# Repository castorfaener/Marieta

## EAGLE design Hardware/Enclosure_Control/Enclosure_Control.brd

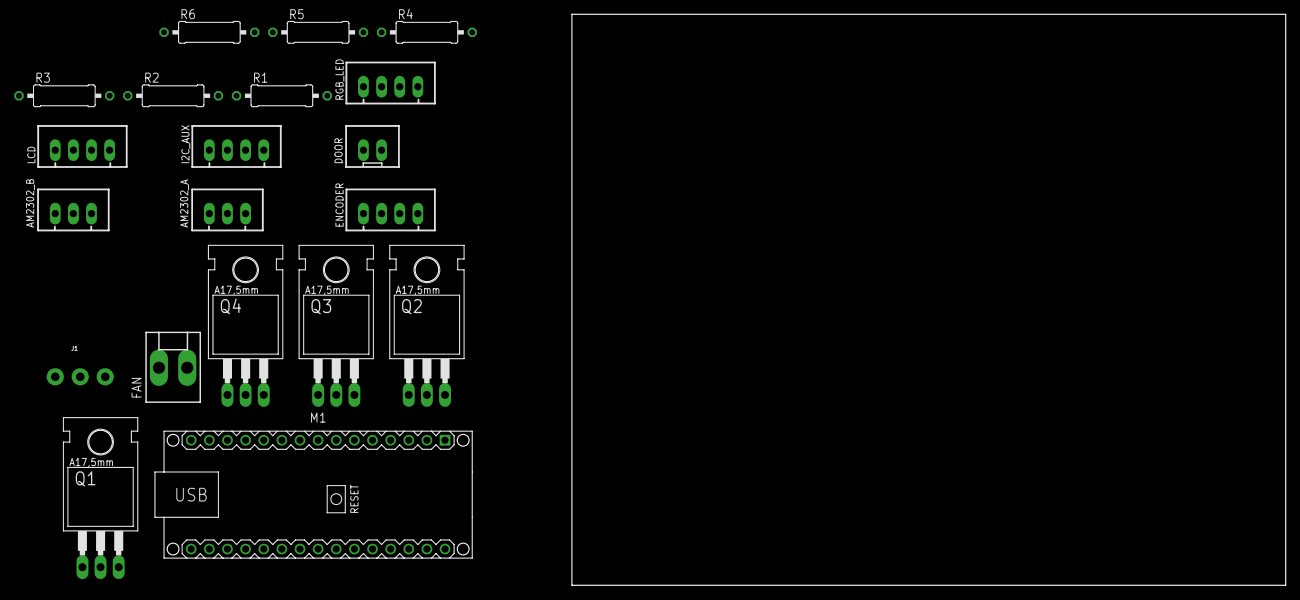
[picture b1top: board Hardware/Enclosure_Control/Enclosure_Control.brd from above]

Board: 2 copper layers, 100.0 x 80.0 mm, 20 parts (0 on the bottom side), 20 nets, no tracks yet.

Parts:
AM2302_A, AM2302_B: JST-XH-03-PIN-LONG-PAD; JST-XH-03-PACKAGE-LONG-PAD
DOOR: JST-XH-02-PIN-LONG-PAD; JST-XH-02-PACKAGE-LONG-PAD
ENCODER: JST-XH-04-PIN-LONG-PAD; JST-XH-04-PACKAGE-LONG-PAD
FAN: KK-156-2
I2C_AUX: JST-XH-04-PIN-LONG-PAD; JST-XH-04-PACKAGE-LONG-PAD
J1: SCREWTERMINAL-3.5MM-3-NS
LCD: JST-XH-04-PIN-LONG-PAD; JST-XH-04-PACKAGE-LONG-PAD
M1: ARDUINO-NANO-3.0
Q1, Q2, Q3, Q4: IRF3704; TO220AH
R1, R6: 0309/12
R2, R3, R4, R5: 10k; 0309/12
RGB_LED: JST-XH-04-PIN-LONG-PAD; JST-XH-04-PACKAGE-LONG-PAD

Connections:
+5V: AM2302_A.1, AM2302_B.1, DOOR.1, I2C_AUX.1, J1.2, LCD.1, M1.J2.1
+12V: FAN.1, J1.3, RGB_LED.1
DHT22_A: AM2302_A.3, M1.J1.11
DHT22_B: AM2302_B.3, M1.J1.10
DOOR_S: DOOR.2, M1.J1.7, R1.2
FAN: M1.J1.13, R5.1
GND: AM2302_A.2, AM2302_B.2, I2C_AUX.2, J1.1, LCD.2, M1.J2.2, Q4.E, R1.1
G_LED: M1.J1.8, R3.1, R4.1
unnamed: Q1.E, Q2.E, Q3.E
unnamed: Q3.C, RGB_LED.4
unnamed: Q2.C, RGB_LED.3
unnamed: Q1.C, RGB_LED.2
unnamed: Q1.B, R2.2
unnamed: Q2.B, R3.2
unnamed: Q3.B, R4.2
unnamed: FAN.2, Q4.C
unnamed: Q4.B, R5.2
R_LED: M1.J1.9, R2.1
SCL: I2C_AUX.4, LCD.4, M1.J2.7
SDA: I2C_AUX.3, LCD.3, M1.J2.8

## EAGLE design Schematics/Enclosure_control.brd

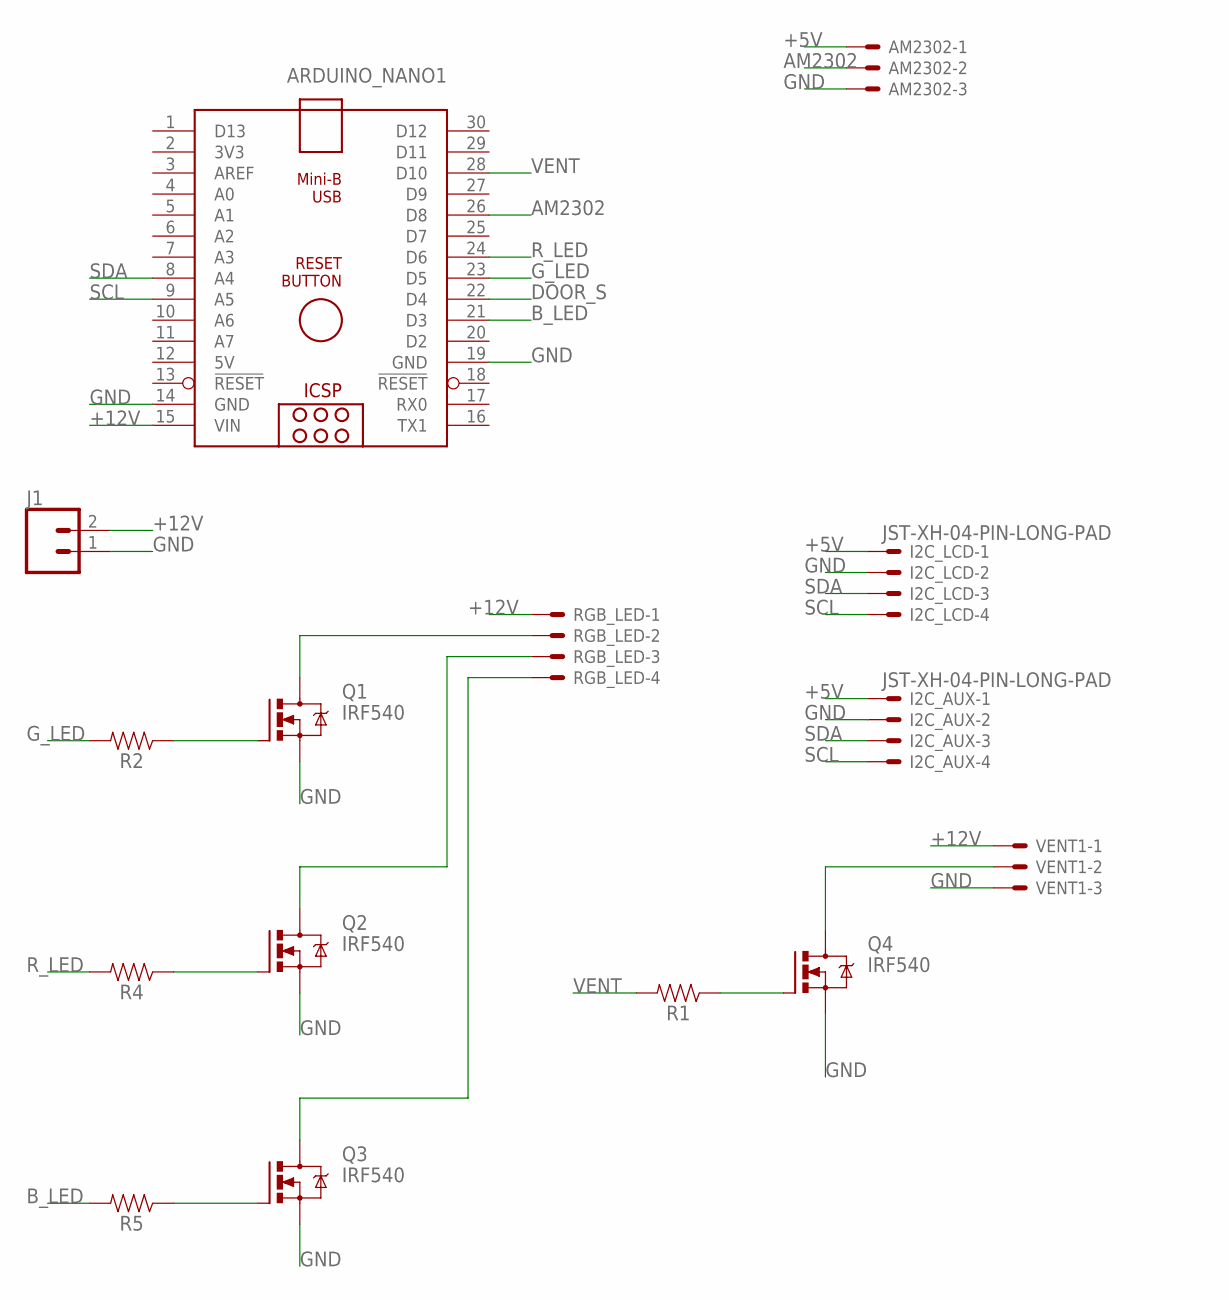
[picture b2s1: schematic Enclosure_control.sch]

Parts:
AM2302: KK-156-3
ARDUINO_NANO1: ARDUINO_NANO
I2C_AUX, I2C_LCD: JST-XH-04-PIN-LONG-PAD; JST-XH-04-PACKAGE-LONG-PAD
J1: CONN_02PTH4; 1X02_XTRA_BIG
Q1, Q2, Q3, Q4: IRF540; TO220BV
R1, R2, R4, R5: AXIAL-0.3
RGB_LED: KK-156-4
VENT1: KK-156-3

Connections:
5V: ARDUINO_NANO1.12 (5V)
+5V: AM2302.1, I2C_AUX.1, I2C_LCD.1
+12V: ARDUINO_NANO1.15 (VIN), J1.2, RGB_LED.1, VENT1.1
AM2302: AM2302.2, ARDUINO_NANO1.26 (D8)
B_LED: ARDUINO_NANO1.21 (D3), R5.P$2 (2)
DOOR_S: ARDUINO_NANO1.22 (D4)
GND: AM2302.3, ARDUINO_NANO1.14 (GND), ARDUINO_NANO1.19 (GND), I2C_AUX.2, I2C_LCD.2, J1.1, Q1.S, Q2.S, Q3.S, Q4.S, VENT1.3
G_LED: ARDUINO_NANO1.23 (D5), R2.P$2 (2)
unnamed: Q2.D, RGB_LED.3
unnamed: Q2.G, R4.P$1 (1)
unnamed: Q3.D, RGB_LED.4
unnamed: Q3.G, R5.P$1 (1)
unnamed: Q4.D, VENT1.2
unnamed: Q4.G, R1.P$1 (1)
unnamed: Q1.G, R2.P$1 (1)
unnamed: Q1.D, RGB_LED.2
R_LED: ARDUINO_NANO1.24 (D6), R4.P$2 (2)
SCL: ARDUINO_NANO1.9 (A5), I2C_AUX.4, I2C_LCD.4
SDA: ARDUINO_NANO1.8 (A4), I2C_AUX.3, I2C_LCD.3
VENT: ARDUINO_NANO1.28 (D10), R1.P$2 (2)

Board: 2 copper layers, 15 parts (0 on the bottom side), 18 nets, no tracks yet.

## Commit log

2020-09-16 Subimos todos los archivos
2020-09-16 Añadimos README.md
2020-09-16 funcion Fan
2020-09-16 Funcion RGB
2020-09-17 Añadimos esquematico
2020-09-18 Añadimos funcion Encoder
2020-09-18 Añadimos funcion menu
2020-10-18 Añadimos archivos de cableado
2020-10-19 Cableado de motores
2021-05-14 Modificando conexiones de cables
2021-05-18 Fan & Pos Cable added
2021-05-18 Añadimos hardware
2021-05-21 Añadimos Extruder_Hotend cable

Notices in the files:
parts and their libraries:
SparkFun-Connectors: Licensing: Creative Commons ShareAlike 4.0 International - https://creativecommons.org/licenses/by-sa/4.0
diy-modules: Released under the Creative Commons Attribution 4.0 International License: http://creativecommons.org/licenses/by/4.0
